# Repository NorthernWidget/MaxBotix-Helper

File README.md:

# MaxBotix-Helper
This board connects to a MaxBotix "weather-resistant" series ultrasonic rangefinder to present a friendlier set of output pins with screw terminals for easy hookup.

| **Top** | **Bottom** |
| ------- | ---------- |
|  |  |

(Images rendered by OSHPark)

### Materials for full assembly
* 1 MaxBotix ultrasonic rangefinder (https://www.maxbotix.com/)
* (Optional) 1 MaxBotix "MaxTemp" temperature correction (https://www.maxbotix.com/Ultrasonic_Sensors/MB7955.htm)
* 1 1x6 screw terminal block, 0.1" spacing (https://www.digikey.com/product-detail/en/on-shore-technology-inc/OSTVN06A150/ED10565-ND/1588866)
* 1 1x7 stubby male header (https://www.digikey.com/product-detail/en/samtec-inc/TSW-107-06-T-S/SAM1027-07-ND/1101220)

### Pins
* **GND:** Ground
* **TC:** Temperature correction for optional MaxTemp sensor
* **SIG:** Signal, selectable to *analog* or *serial* (UART) based on solder jumper connection
* **V+:** Input voltage

### Features
* 1 3-pin output for the temperature correction (2x GND + 1x TC)
* 1 3-pin output for the data logger or other microcontroller, etc. interface (GND, V+, SIG)
* Includes the proper number of ground connections to link both the temperature correction and the data logger to the MaxBotix rangefinder (3 instead of 1)
* Selectable output: analog voltage or serial signal

### Instructions
* User solder to select an analog or serial output on bottom side of the board
* Solder the male header terminal onto the top side of the board
* Using the male header terminal block, solder the MaxBotix-Helper to your MaxBotix rangefinder, oriented such such that the black plastic piece in the center lies along the widest point of the threaded circular housing. If you are unsure, match up the white square on our Helper with the square pin on the MaxBotix solder rings. This is the critical piece: otherwise, the new assembly will not fit in a 3/4" pipe, according to the sensor threading!
* Solder the screw terminal block onto the top side of the board (you can also do this earlier, depending on when it is easier for you). This should be in the position that makes it centered within the threaded circular ring.

That's it! At this point, you should be ready connect your data logger / MCU device and the optional MaxTemp sensor. The last steps are just to ruggedize your sensor if you use it outside: we recommend press-fit PVC connections to prevent the wire-to-board connections from shearing off, and to use a solar radiation shield for the temperature compensation sensor.

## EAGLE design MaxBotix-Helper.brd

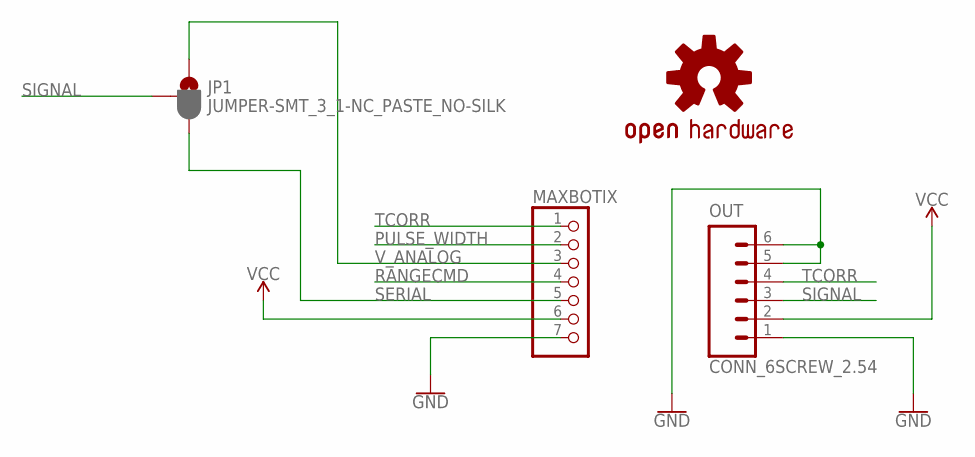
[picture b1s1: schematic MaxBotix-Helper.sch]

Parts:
JP1: JUMPER-SMT_3_1-NC_PASTE_NO-SILK; SMT-JUMPER_3_1-NC_PASTE_NO-SILK
LOGO1: OSHW-LOGOS; OSHW-LOGO-S
MAXBOTIX: CONN_7; 1X07
OUT: CONN_6SCREW_2.54; 1X06_SCREW

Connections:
GND: MAXBOTIX.7, OUT.1, OUT.5, OUT.6
PULSE_WIDTH: MAXBOTIX.2
RANGECMD: MAXBOTIX.4
SERIAL: JP1.3, MAXBOTIX.5
SIGNAL: JP1.2, OUT.3
TCORR: MAXBOTIX.1, OUT.4
VCC: MAXBOTIX.6, OUT.2
V_ANALOG: JP1.1, MAXBOTIX.3

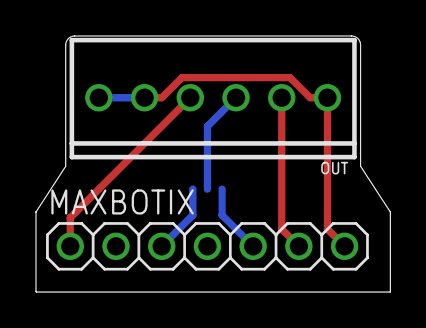
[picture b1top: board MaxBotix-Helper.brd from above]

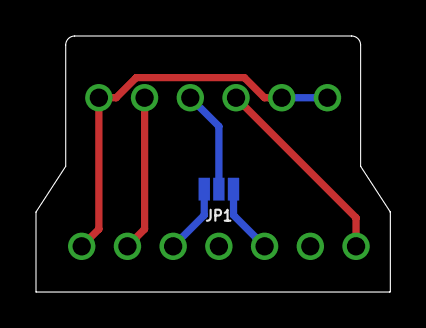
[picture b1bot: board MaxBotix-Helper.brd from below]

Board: 2 copper layers, 19.7 x 14.2 mm, 4 parts (2 on the bottom side), 6 nets.

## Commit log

2019-03-21 CC-BY-SA 4.0
2019-03-21 Initial design
2019-03-21 Silk screen cleanup
    Cleaned up/reorganized the silkscreen
2019-03-21 Name, date, company, version
2019-03-21 Move signal select etc. to not be behind MB board
2019-03-21 OSH Park style
2019-03-21 Aesthetics
2019-04-28 Screw terminal labels: both sides
2019-04-28 Figures for upcoming README
2019-04-28 Description and instructions
2019-04-28 square to square
2022-03-08 Zenodo DOI badge
2022-03-08 Cite Zenodo DOI

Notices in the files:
parts and their libraries:
SparkFun-Jumpers: Licensing: Creative Commons ShareAlike 4.0 International - https://creativecommons.org/licenses/by-sa/4.0
